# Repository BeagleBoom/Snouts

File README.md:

# 

----
----

**CURRENTLY BROKEN, DO NOT USE OR YOUR BEAGLE BONE COULD BREAK**
>The PCB currently contains a bug with the power-supply which could kill your beagle boom :-/

----
----

This repository contains the BeagleBoom Snouts' PCB layouts.

# About this repository
This repository is part of the [BeagleBoom](https://github.com/beagleboom)-Sampler project developed by the academic working group "[Creative Technologies AG](http://www.creative-technologies.de/)" (ctag) at the [University of Applied Sciences Kiel](https://www.fh-kiel.de/).

The `Sampler` folder holds the PCB which is connected to the BeagleBone. It holds the power source, adc and level shifter.
The `Sampler UI` folder contains the front PCB with all the buttons, jacks, rotaries and lcd port, with all the needed resistors. 

# License
The content and source code of this project itself is licensed under the [Creative Commons Attribution 4.0 International license](https://creativecommons.org/licenses/by/4.0/).

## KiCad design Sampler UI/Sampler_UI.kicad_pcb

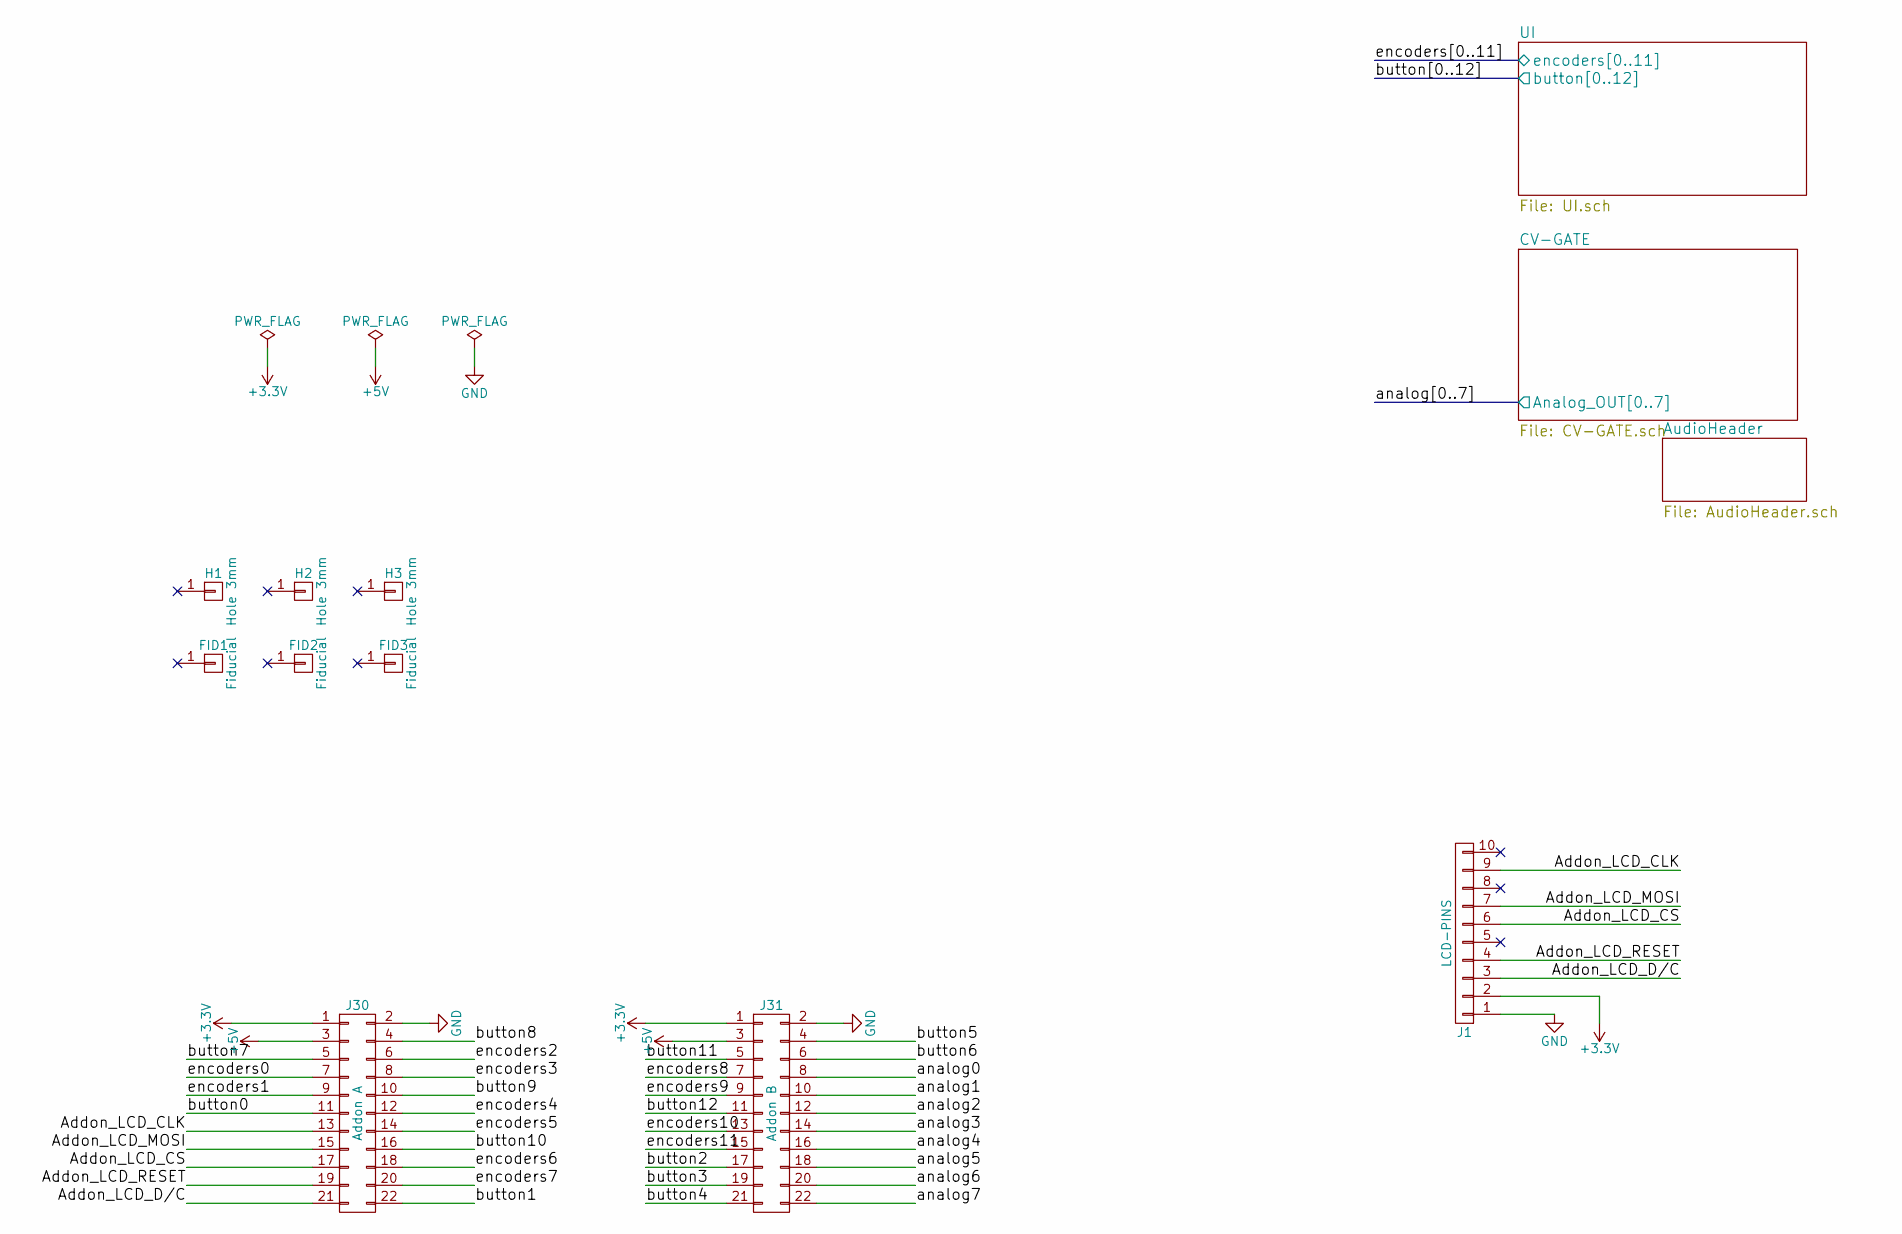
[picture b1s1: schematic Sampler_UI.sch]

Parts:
FID1, FID2, FID3: Fiducial; Fiducial_1mm_Dia_2.54mm_Outer_CopperTop
H1, H2, H3: Hole 3mm; hole_3mm
J1: LCD-PINS; Pin_Header_Straight_1x10_Pitch2.54mm
J30: Addon A; Pin_Header_Straight_2x11_Pitch2.54mm
J31: Addon B; Pin_Header_Straight_2x11_Pitch2.54mm

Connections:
+3V3: J1.2, J30.1, J31.1; also elsewhere on the board
+5V: J30.3, J31.3; also elsewhere on the board
/Addon_LCD_CLK: J1.9, J30.13
/Addon_LCD_CS: J1.6, J30.17
/Addon_LCD_D/C: J1.3, J30.21
/Addon_LCD_MOSI: J1.7, J30.15
/Addon_LCD_RESET: J1.4, J30.19
/analog0: J31.8; also elsewhere on the board
/analog1: J31.10; also elsewhere on the board
/analog2: J31.12; also elsewhere on the board
/analog3: J31.14; also elsewhere on the board
/analog4: J31.16; also elsewhere on the board
/analog5: J31.18; also elsewhere on the board
/analog6: J31.20; also elsewhere on the board
/analog7: J31.22; also elsewhere on the board
/button0: J30.11; also elsewhere on the board
/button1: J30.22; also elsewhere on the board
/button2: J31.17; also elsewhere on the board
/button3: J31.19; also elsewhere on the board
/button4: J31.21; also elsewhere on the board
/button5: J31.4; also elsewhere on the board
/button6: J31.6; also elsewhere on the board
/button7: J30.5; also elsewhere on the board
/button8: J30.4; also elsewhere on the board
/button9: J30.10; also elsewhere on the board
/button10: J30.16; also elsewhere on the board
/button11: J31.5; also elsewhere on the board
/button12: J31.11; also elsewhere on the board
/encoders0: J30.7; also elsewhere on the board
/encoders1: J30.9; also elsewhere on the board
/encoders2: J30.6; also elsewhere on the board
/encoders3: J30.8; also elsewhere on the board
/encoders4: J30.12; also elsewhere on the board
/encoders5: J30.14; also elsewhere on the board
/encoders6: J30.18; also elsewhere on the board
/encoders7: J30.20; also elsewhere on the board
/encoders8: J31.7; also elsewhere on the board
/encoders9: J31.9; also elsewhere on the board
/encoders10: J31.13; also elsewhere on the board
/encoders11: J31.15; also elsewhere on the board
GND: J1.1, J30.2, J31.2; also elsewhere on the board

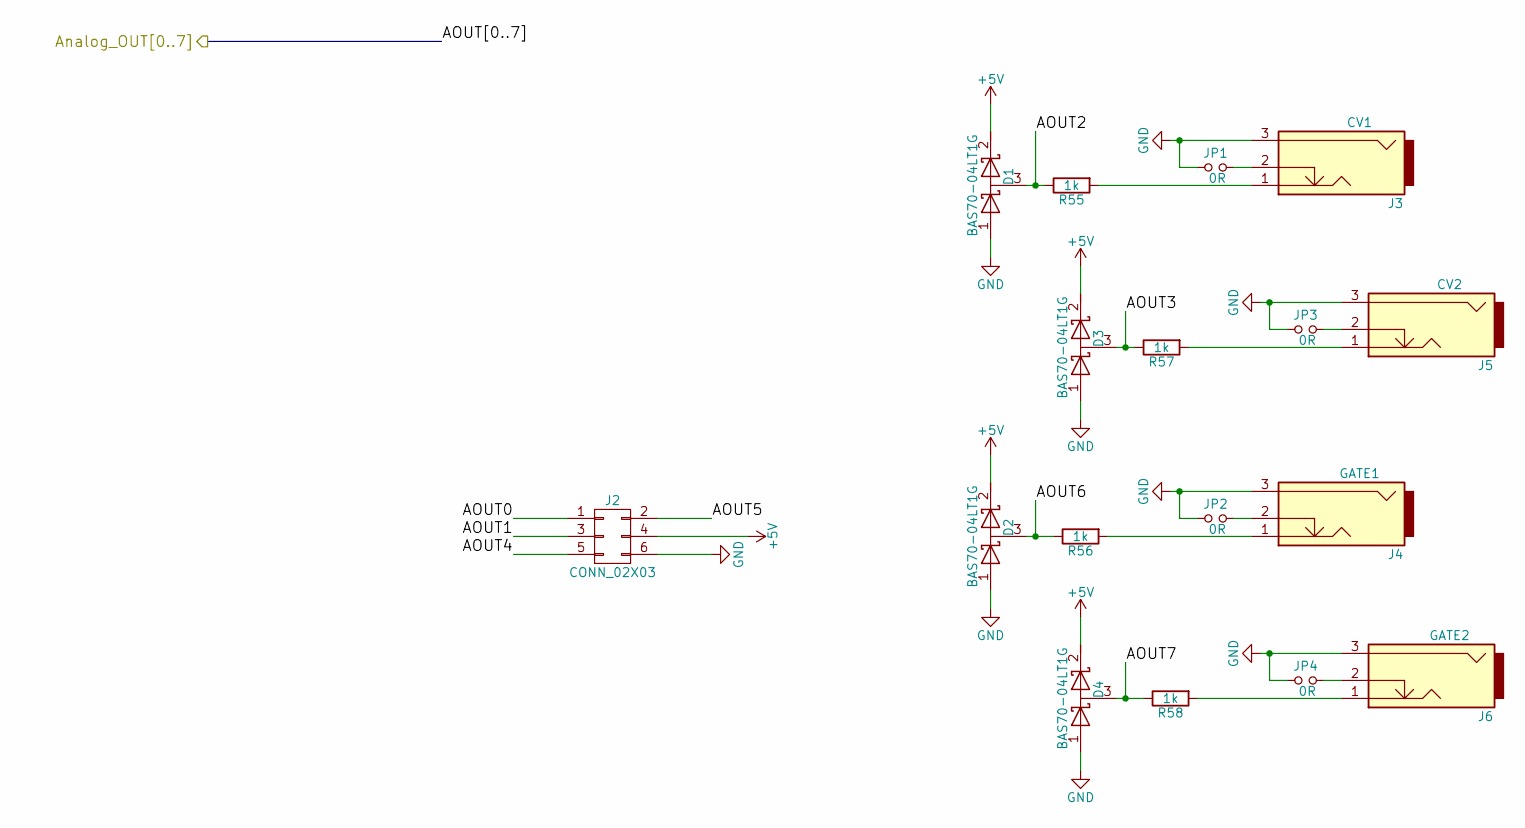
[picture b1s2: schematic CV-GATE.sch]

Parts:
D1, D2, D3, D4: BAS70-04LT1G; SOT-23_Handsoldering
J2: CONN_02X03; Pin_Header_Straight_2x03_Pitch2.54mm
J3: CV1; THONKICONN
J4: GATE1; THONKICONN
J5: CV2; THONKICONN
J6: GATE2; THONKICONN
JP1: 0R; SW_NKK_G1xJP
JP2, JP3, JP4: 0R; C_0603_HandSoldering
R55, R56, R57, R58: 1k; C_0603_HandSoldering

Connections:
+5V: D1.2 (K), D2.2 (K), D3.2 (K), D4.2 (K), J2.4; also elsewhere on the board
/analog0: J2.1; also elsewhere on the board
/analog1: J2.3; also elsewhere on the board
/analog2: D1.3 (common), R55.1; also elsewhere on the board
/analog3: D3.3 (common), R57.1; also elsewhere on the board
/analog4: J2.5; also elsewhere on the board
/analog5: J2.2; also elsewhere on the board
/analog6: D2.3 (common), R56.1; also elsewhere on the board
/analog7: D4.3 (common), R58.1; also elsewhere on the board
GND: D1.1 (A), D2.1 (A), D3.1 (A), D4.1 (A), J2.6, J3.3, J4.3, J5.3, J6.3, JP1.1, JP2.1, JP3.1, JP4.1; also elsewhere on the board
unnamed: J3.1, R55.2
unnamed: J3.2, JP1.2
unnamed: J4.1, R56.2
unnamed: J4.2, JP2.2
unnamed: J5.1, R57.2
unnamed: J5.2, JP3.2
unnamed: J6.1, R58.2
unnamed: J6.2, JP4.2

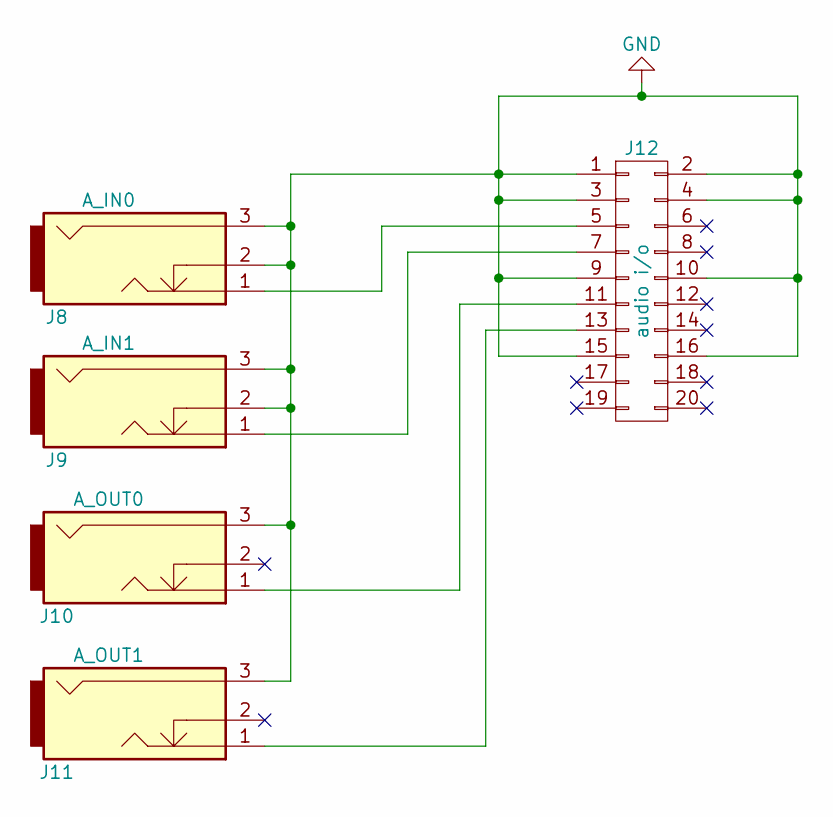
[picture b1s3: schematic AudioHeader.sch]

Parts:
J8: A_IN0; THONKICONN
J9: A_IN1; THONKICONN
J10: A_OUT0; THONKICONN
J11: A_OUT1; THONKICONN
J12: audio i/o; Pin_Header_Straight_2x10_Pitch2.54mm

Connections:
GND: J8.2, J8.3, J9.2, J9.3, J10.3, J11.3, J12.1, J12.2, J12.3, J12.4, J12.9, J12.10, J12.15, J12.16; also elsewhere on the board
unnamed: J10.1, J12.11
unnamed: J11.1, J12.13
unnamed: J8.1, J12.5
unnamed: J9.1, J12.7

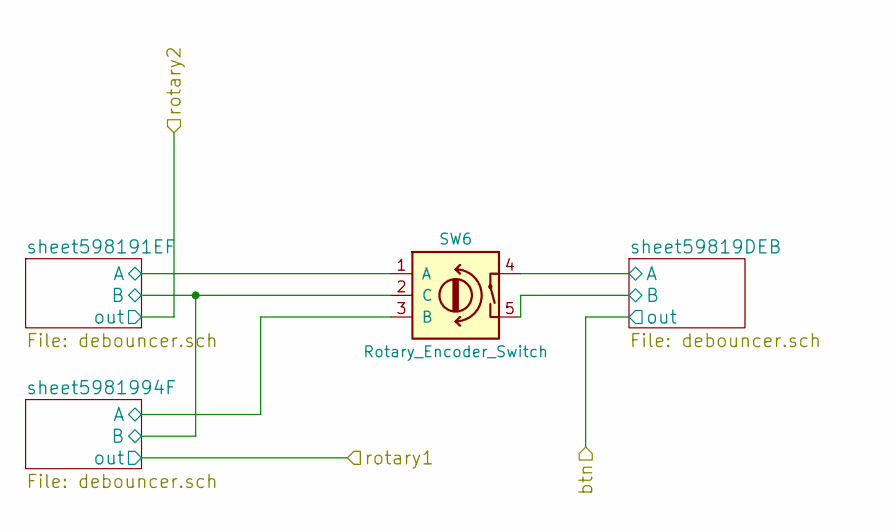
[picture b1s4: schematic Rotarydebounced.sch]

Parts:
SW1: Rotary_Encoder_Switch; ALPS_EC11E

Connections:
/UI/Sheet59818EE0/sheet59819DEB/A: SW1.4; also elsewhere on the board
/UI/Sheet59818EE0/sheet598191EF/A: SW1.1 (A); also elsewhere on the board
/UI/Sheet59818EE0/sheet5981994F/A: SW1.3 (B); also elsewhere on the board
GND: SW1.2 (C), SW1.5; also elsewhere on the board

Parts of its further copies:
SW2, SW3, SW4, SW5, SW6: Rotary_Encoder_Switch; ALPS_EC11E

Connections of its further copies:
/UI/sheet5981BCBF/sheet59819DEB/A: SW2.4; also elsewhere on the board
/UI/sheet5981BCBF/sheet598191EF/A: SW2.1 (A); also elsewhere on the board
/UI/sheet5981BCBF/sheet5981994F/A: SW2.3 (B); also elsewhere on the board
/UI/sheet5981BE21/sheet59819DEB/A: SW3.4; also elsewhere on the board
/UI/sheet5981BE21/sheet598191EF/A: SW3.1 (A); also elsewhere on the board
/UI/sheet5981BE21/sheet5981994F/A: SW3.3 (B); also elsewhere on the board
/UI/sheet5981BFDD/sheet59819DEB/A: SW4.4; also elsewhere on the board
/UI/sheet5981BFDD/sheet598191EF/A: SW4.1 (A); also elsewhere on the board
/UI/sheet5981BFDD/sheet5981994F/A: SW4.3 (B); also elsewhere on the board
/UI/sheet5981C76E/sheet59819DEB/A: SW6.4; also elsewhere on the board
/UI/sheet5981C76E/sheet598191EF/A: SW6.1 (A); also elsewhere on the board
/UI/sheet5981C76E/sheet5981994F/A: SW6.3 (B); also elsewhere on the board
/UI/sheet5981C561/sheet59819DEB/A: SW5.4; also elsewhere on the board
/UI/sheet5981C561/sheet598191EF/A: SW5.1 (A); also elsewhere on the board
/UI/sheet5981C561/sheet5981994F/A: SW5.3 (B); also elsewhere on the board
GND: SW2.2 (C), SW2.5, SW3.2 (C), SW3.5, SW4.2 (C), SW4.5, SW5.2 (C), SW5.5, SW6.2 (C), SW6.5; also elsewhere on the board

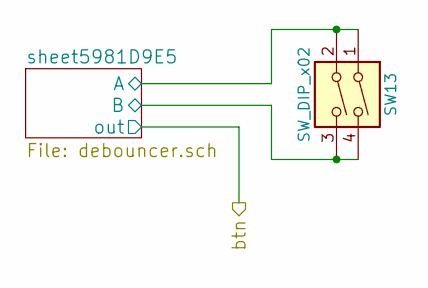
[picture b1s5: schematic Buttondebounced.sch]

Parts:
SW7: SW_DIP_x02; TL1105

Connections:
/UI/Sheet5981D5D9/sheet5981D9E5/A: SW7.1, SW7.2; also elsewhere on the board
GND: SW7.3, SW7.4; also elsewhere on the board

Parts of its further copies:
SW8, SW9, SW10, SW11, SW12, SW13: SW_DIP_x02; TL1105

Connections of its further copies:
/UI/sheet5981FF0E/sheet5981D9E5/A: SW8.1, SW8.2; also elsewhere on the board
/UI/sheet5981FFD8/sheet5981D9E5/A: SW9.1, SW9.2; also elsewhere on the board
/UI/sheet598200A2/sheet5981D9E5/A: SW10.1, SW10.2; also elsewhere on the board
/UI/sheet598202F9/sheet5981D9E5/A: SW11.1, SW11.2; also elsewhere on the board
/UI/sheet598203D2/sheet5981D9E5/A: SW12.1, SW12.2; also elsewhere on the board
/UI/sheet598204B4/sheet5981D9E5/A: SW13.1, SW13.2; also elsewhere on the board
GND: SW8.3, SW8.4, SW9.3, SW9.4, SW10.3, SW10.4, SW11.3, SW11.4, SW12.3, SW12.4, SW13.3, SW13.4; also elsewhere on the board

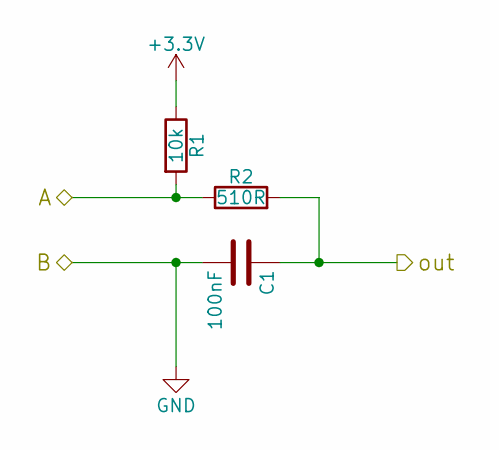
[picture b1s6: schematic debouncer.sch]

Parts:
C1: 100nF; C_0603_HandSoldering
R1: 10k; C_0603_HandSoldering
R2: 510R; C_0603_HandSoldering

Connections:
+3V3: R1.1; also elsewhere on the board
/UI/Sheet59818EE0/sheet598191EF/A: R1.2, R2.1; also elsewhere on the board
/encoders1: C1.1, R2.2; also elsewhere on the board
GND: C1.2; also elsewhere on the board

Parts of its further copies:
C2, C3, C4, C5, C6, C7, C8, C9, C10, C11, C12, C13, C14, C15, C16, C17, C18, C19, C20, C21, C22, C23, C24, C25: 100nF; C_0603_HandSoldering
R3, R5, R7, R9, R11, R13, R15, R17, R19, R21, R23, R25, R27, R29, R31, R33, R35, R37, R39, R41, R43, R45, R47, R49: 10k; C_0603_HandSoldering
R4, R6, R8, R10, R12, R14, R16, R18, R20, R22, R24, R26, R28, R30, R32, R34, R36, R38, R40, R42, R44, R46, R48, R50: 510R; C_0603_HandSoldering

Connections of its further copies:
+3V3: R3.1, R5.1, R7.1, R9.1, R11.1, R13.1, R15.1, R17.1, R19.1, R21.1, R23.1, R25.1, R27.1, R29.1, R31.1, R33.1, R35.1, R37.1, R39.1, R41.1, R43.1, R45.1, R47.1, R49.1; also elsewhere on the board
/UI/Sheet5981D5D9/sheet5981D9E5/A: R37.2, R38.1; also elsewhere on the board
/UI/Sheet59818EE0/sheet59819DEB/A: R5.2, R6.1; also elsewhere on the board
/UI/Sheet59818EE0/sheet5981994F/A: R3.2, R4.1; also elsewhere on the board
/UI/sheet5981BCBF/sheet59819DEB/A: R11.2, R12.1; also elsewhere on the board
/UI/sheet5981BCBF/sheet598191EF/A: R7.2, R8.1; also elsewhere on the board
/UI/sheet5981BCBF/sheet5981994F/A: R9.2, R10.1; also elsewhere on the board
/UI/sheet5981BE21/sheet59819DEB/A: R17.2, R18.1; also elsewhere on the board
/UI/sheet5981BE21/sheet598191EF/A: R13.2, R14.1; also elsewhere on the board
/UI/sheet5981BE21/sheet5981994F/A: R15.2, R16.1; also elsewhere on the board
/UI/sheet5981BFDD/sheet59819DEB/A: R23.2, R24.1; also elsewhere on the board
/UI/sheet5981BFDD/sheet598191EF/A: R19.2, R20.1; also elsewhere on the board
/UI/sheet5981BFDD/sheet5981994F/A: R21.2, R22.1; also elsewhere on the board
/UI/sheet5981C76E/sheet59819DEB/A: R35.2, R36.1; also elsewhere on the board
/UI/sheet5981C76E/sheet598191EF/A: R31.2, R32.1; also elsewhere on the board
/UI/sheet5981C76E/sheet5981994F/A: R33.2, R34.1; also elsewhere on the board
/UI/sheet5981C561/sheet59819DEB/A: R29.2, R30.1; also elsewhere on the board
/UI/sheet5981C561/sheet598191EF/A: R25.2, R26.1; also elsewhere on the board
/UI/sheet5981C561/sheet5981994F/A: R27.2, R28.1; also elsewhere on the board
/UI/sheet5981FF0E/sheet5981D9E5/A: R39.2, R40.1; also elsewhere on the board
/UI/sheet5981FFD8/sheet5981D9E5/A: R41.2, R42.1; also elsewhere on the board
/UI/sheet598200A2/sheet5981D9E5/A: R43.2, R44.1; also elsewhere on the board
/UI/sheet598202F9/sheet5981D9E5/A: R45.2, R46.1; also elsewhere on the board
/UI/sheet598203D2/sheet5981D9E5/A: R47.2, R48.1; also elsewhere on the board
/UI/sheet598204B4/sheet5981D9E5/A: R49.2, R50.1; also elsewhere on the board
/button0: C19.1, R38.2; also elsewhere on the board
/button1: C20.1, R40.2; also elsewhere on the board
/button2: C21.1, R42.2; also elsewhere on the board
/button3: C22.1, R44.2; also elsewhere on the board
/button4: C23.1, R46.2; also elsewhere on the board
/button5: C24.1, R48.2; also elsewhere on the board
/button6: C25.1, R50.2; also elsewhere on the board
/button7: C3.1, R6.2; also elsewhere on the board
/button8: C6.1, R12.2; also elsewhere on the board
/button9: C9.1, R18.2; also elsewhere on the board
/button10: C12.1, R24.2; also elsewhere on the board
/button11: C15.1, R30.2; also elsewhere on the board
/button12: C18.1, R36.2; also elsewhere on the board
/encoders0: C2.1, R4.2; also elsewhere on the board
/encoders2: C5.1, R10.2; also elsewhere on the board
/encoders3: C4.1, R8.2; also elsewhere on the board
/encoders4: C8.1, R16.2; also elsewhere on the board
/encoders5: C7.1, R14.2; also elsewhere on the board
/encoders6: C11.1, R22.2; also elsewhere on the board
/encoders7: C10.1, R20.2; also elsewhere on the board
/encoders8: C14.1, R28.2; also elsewhere on the board
/encoders9: C13.1, R26.2; also elsewhere on the board
/encoders10: C17.1, R34.2; also elsewhere on the board
/encoders11: C16.1, R32.2; also elsewhere on the board
GND: C2.2, C3.2, C4.2, C5.2, C6.2, C7.2, C8.2, C9.2, C10.2, C11.2, C12.2, C13.2, C14.2, C15.2, C16.2, C17.2, C18.2, C19.2, C20.2, C21.2, C22.2, C23.2, C24.2, C25.2; also elsewhere on the board

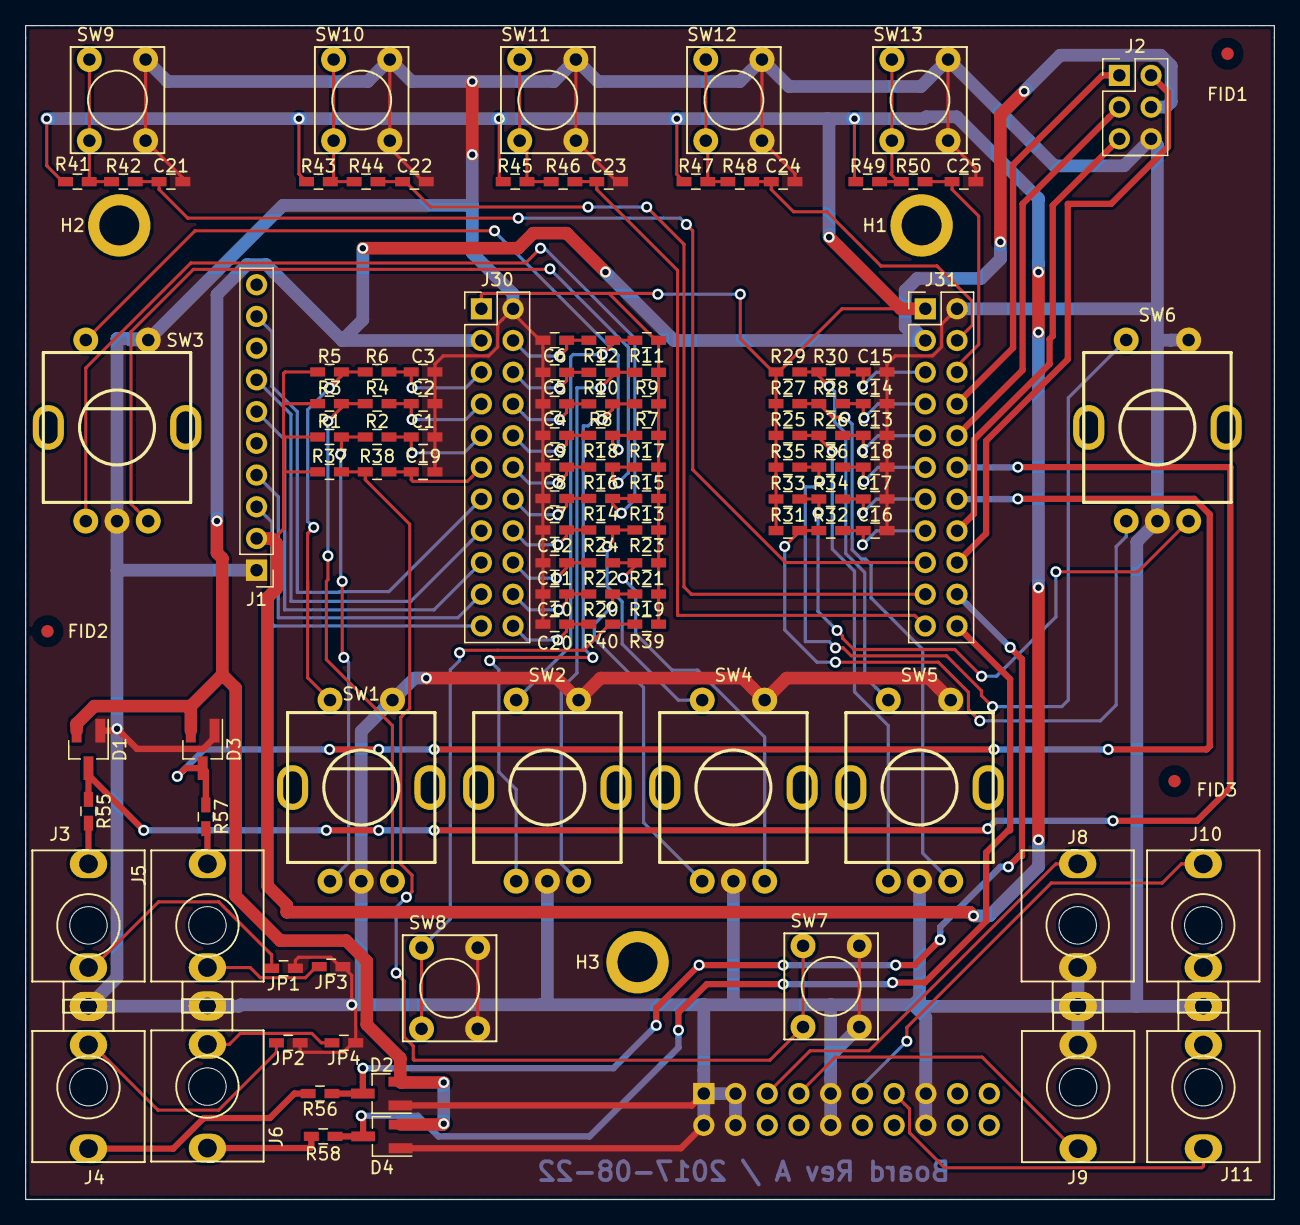
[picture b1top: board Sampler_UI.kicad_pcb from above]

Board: 2 copper layers, 100.0 x 94.0 mm, 119 parts (1 on the bottom side), 78 nets.

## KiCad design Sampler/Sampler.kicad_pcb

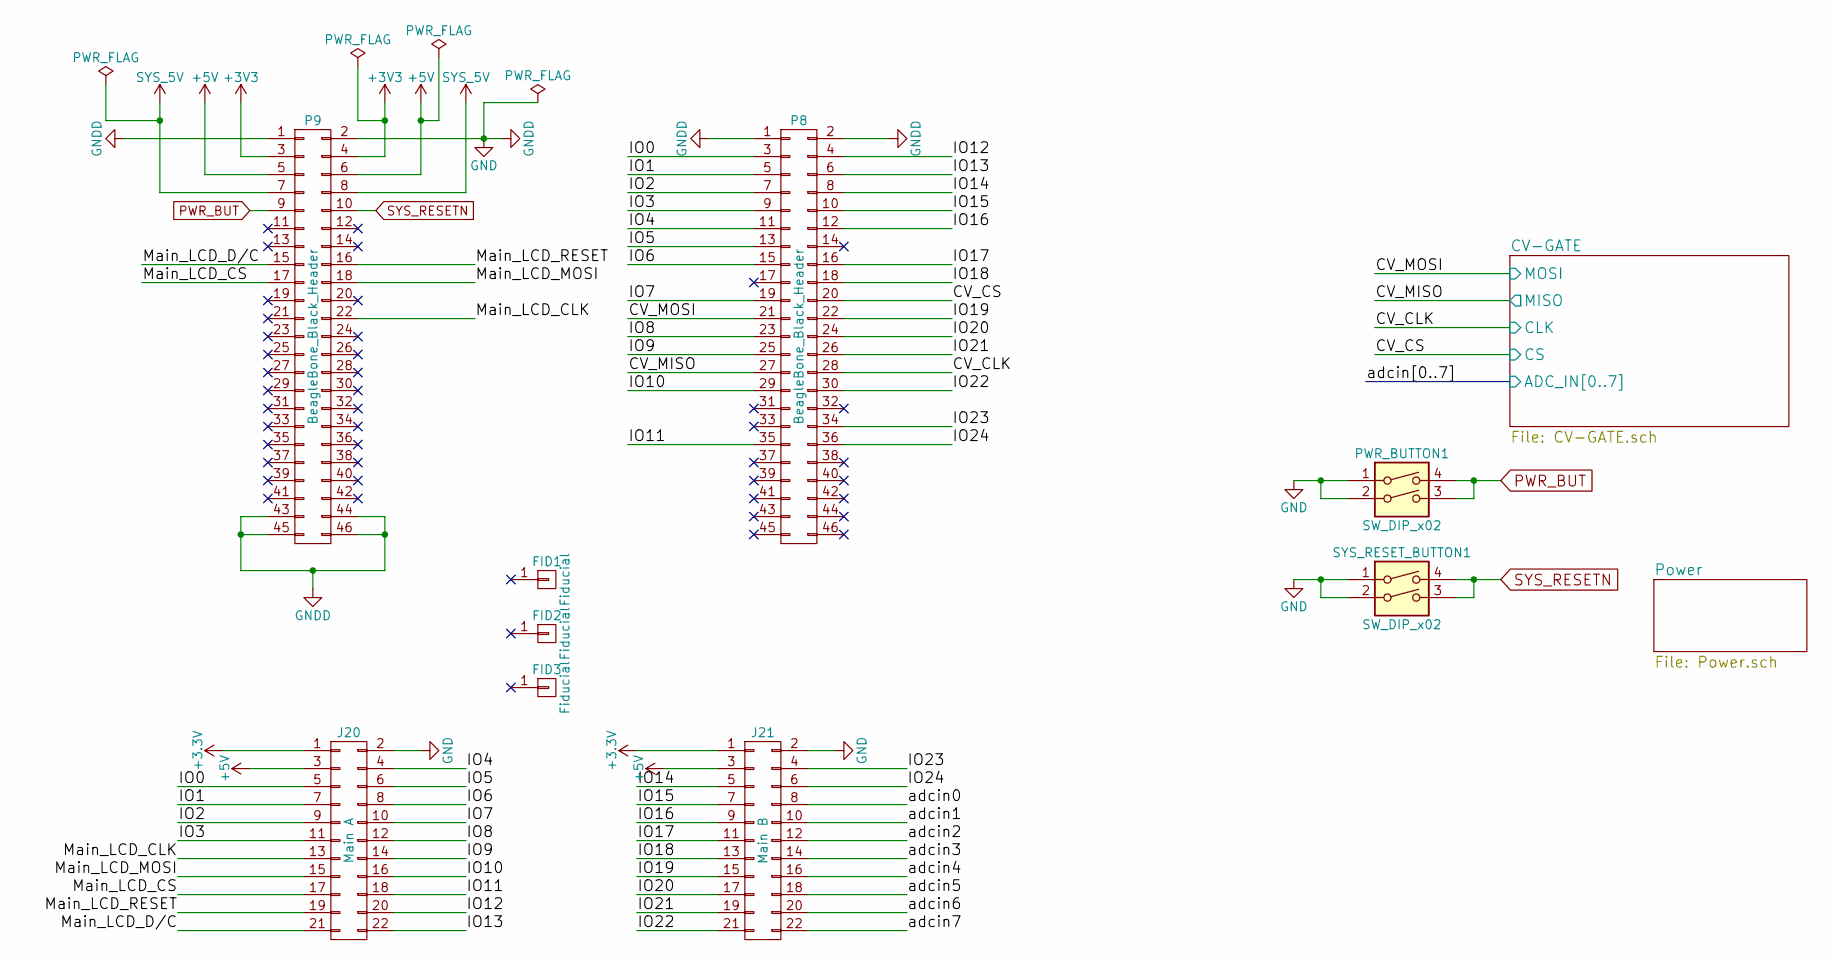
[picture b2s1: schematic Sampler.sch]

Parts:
FID1, FID2, FID3: Fiducial; Fiducial_1mm_Dia_2.54mm_Outer_CopperTop
J20: Main A; Pin_Header_Straight_2x11_Pitch2.54mm
J21: Main B; Pin_Header_Straight_2x11_Pitch2.54mm
P8, P9: BeagleBone_Black_Header; Socket_BeagleBone_Black
PWR_BUTTON1: SW_DIP_x02; TL1105
SYS_RESET_BUTTON1: SW_DIP_x02; TL1105

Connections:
+5V: J20.3, J21.3, P9.5, P9.6; also elsewhere on the board
/CV_CLK: P8.28; also elsewhere on the board
/CV_CS: P8.20; also elsewhere on the board
/CV_MISO: P8.27; also elsewhere on the board
/CV_MOSI: P8.21; also elsewhere on the board
/IO0: J20.5, P8.3
/IO1: J20.7, P8.5
/IO2: J20.9, P8.7
/IO3: J20.11, P8.9
/IO4: J20.4, P8.11
/IO5: J20.6, P8.13
/IO6: J20.8, P8.15
/IO7: J20.10, P8.19
/IO8: J20.12, P8.23
/IO9: J20.14, P8.25
/IO10: J20.16, P8.29
/IO11: J20.18, P8.35
/IO12: J20.20, P8.4
/IO13: J20.22, P8.6
/IO14: J21.5, P8.8
/IO15: J21.7, P8.10
/IO16: J21.9, P8.12
/IO17: J21.11, P8.16
/IO18: J21.13, P8.18
/IO19: J21.15, P8.22
/IO20: J21.17, P8.24
/IO21: J21.19, P8.26
/IO22: J21.21, P8.30
/IO23: J21.4, P8.34
/IO24: J21.6, P8.36
/Main_LCD_CLK: J20.13, P9.22
/Main_LCD_CS: J20.17, P9.17
/Main_LCD_D/C: J20.21, P9.15
/Main_LCD_MOSI: J20.15, P9.18
/Main_LCD_RESET: J20.19, P9.16
/adcin0: J21.8; also elsewhere on the board
/adcin1: J21.10; also elsewhere on the board
/adcin2: J21.12; also elsewhere on the board
/adcin3: J21.14; also elsewhere on the board
/adcin4: J21.16; also elsewhere on the board
/adcin5: J21.18; also elsewhere on the board
/adcin6: J21.20; also elsewhere on the board
/adcin7: J21.22; also elsewhere on the board
GND: J20.2, J21.2, P8.1, P8.2, P9.1, P9.2, P9.43, P9.44, P9.45, P9.46, PWR_BUTTON1.1, PWR_BUTTON1.2, SYS_RESET_BUTTON1.1, SYS_RESET_BUTTON1.2; also elsewhere on the board
PWR_BUT: P9.9, PWR_BUTTON1.3, PWR_BUTTON1.4
SYS_5V: P9.7, P9.8
SYS_RESETN: P9.10, SYS_RESET_BUTTON1.3, SYS_RESET_BUTTON1.4

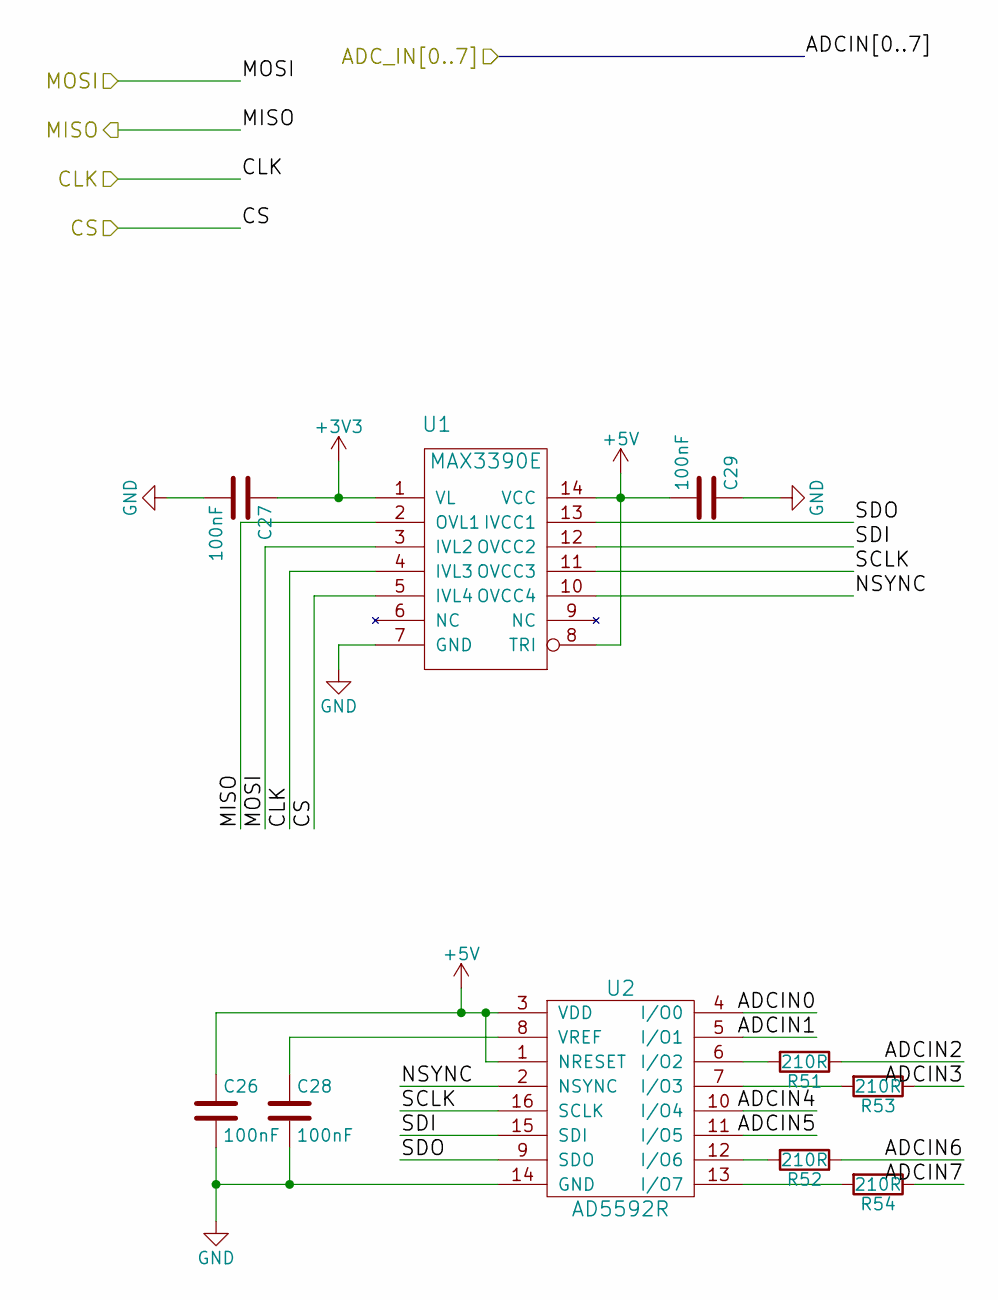
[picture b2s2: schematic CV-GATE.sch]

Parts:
C26, C27, C28, C29: 100nF; C_0603_HandSoldering
R51, R52, R53, R54: 210R; C_0603_HandSoldering
U1: MAX3390E; TSSOP-14_4.4x5mm_Pitch0.65mm
U2: AD5592R; TSSOP-16_4.4x5mm_Pitch0.65mm

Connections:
+5V: C26.1, C29.2, U1.8 (TRI), U1.14 (VCC), U2.1 (NRESET), U2.3 (VDD); also elsewhere on the board
/CV-GATE/NSYNC: U1.10 (OVCC4), U2.2 (NSYNC)
/CV-GATE/SCLK: U1.11 (OVCC3), U2.16 (SCLK)
/CV-GATE/SDI: U1.12 (OVCC2), U2.15 (SDI)
/CV-GATE/SDO: U1.13 (IVCC1), U2.9 (SDO)
/CV_CLK: U1.4 (IVL3); also elsewhere on the board
/CV_CS: U1.5 (IVL4); also elsewhere on the board
/CV_MISO: U1.2 (OVL1); also elsewhere on the board
/CV_MOSI: U1.3 (IVL2); also elsewhere on the board
/adcin0: U2.4 (I/O0); also elsewhere on the board
/adcin1: U2.5 (I/O1); also elsewhere on the board
/adcin2: R51.1; also elsewhere on the board
/adcin3: R53.1; also elsewhere on the board
/adcin4: U2.10 (I/O4); also elsewhere on the board
/adcin5: U2.11 (I/O5); also elsewhere on the board
/adcin6: R52.1; also elsewhere on the board
/adcin7: R54.1; also elsewhere on the board
GND: C26.2, C27.2, C28.2, C29.1, U1.7 (GND), U2.14 (GND); also elsewhere on the board
unnamed: C28.1, U2.8 (VREF)
unnamed: R51.2, U2.6 (I/O2)
unnamed: R52.2, U2.12 (I/O6)
unnamed: R53.2, U2.7 (I/O3)
unnamed: R54.2, U2.13 (I/O7)

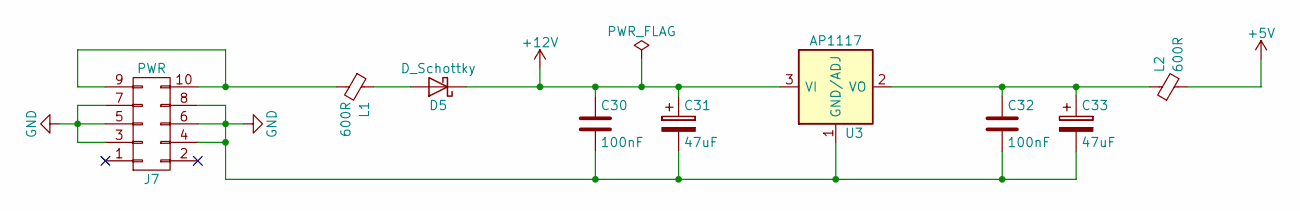
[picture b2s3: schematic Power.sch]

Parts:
C30, C32: 100nF; C_0603_HandSoldering
C31, C33: 47uF; CP_Elec_8x5.4
D5: D_Schottky; D_SOD-323_HandSoldering
J7: PWR; Pin_Header_Straight_2x05_Pitch2.54mm
L1, L2: 600R; C_0805_HandSoldering
U3: AP1117; SOT-223

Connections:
+5V: L2.2; also elsewhere on the board
+12V: C30.1, C31.1, D5.1 (K), U3.3 (VI)
GND: C30.2, C31.2, C32.2, C33.2, J7.3, J7.4, J7.5, J7.6, J7.7, J7.8, U3.1 (GND/ADJ); also elsewhere on the board
unnamed: C32.1, C33.1, L2.1, U3.2 (VO), U3.4 (VO)
unnamed: D5.2 (A), L1.1
unnamed: J7.9, J7.10, L1.2

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
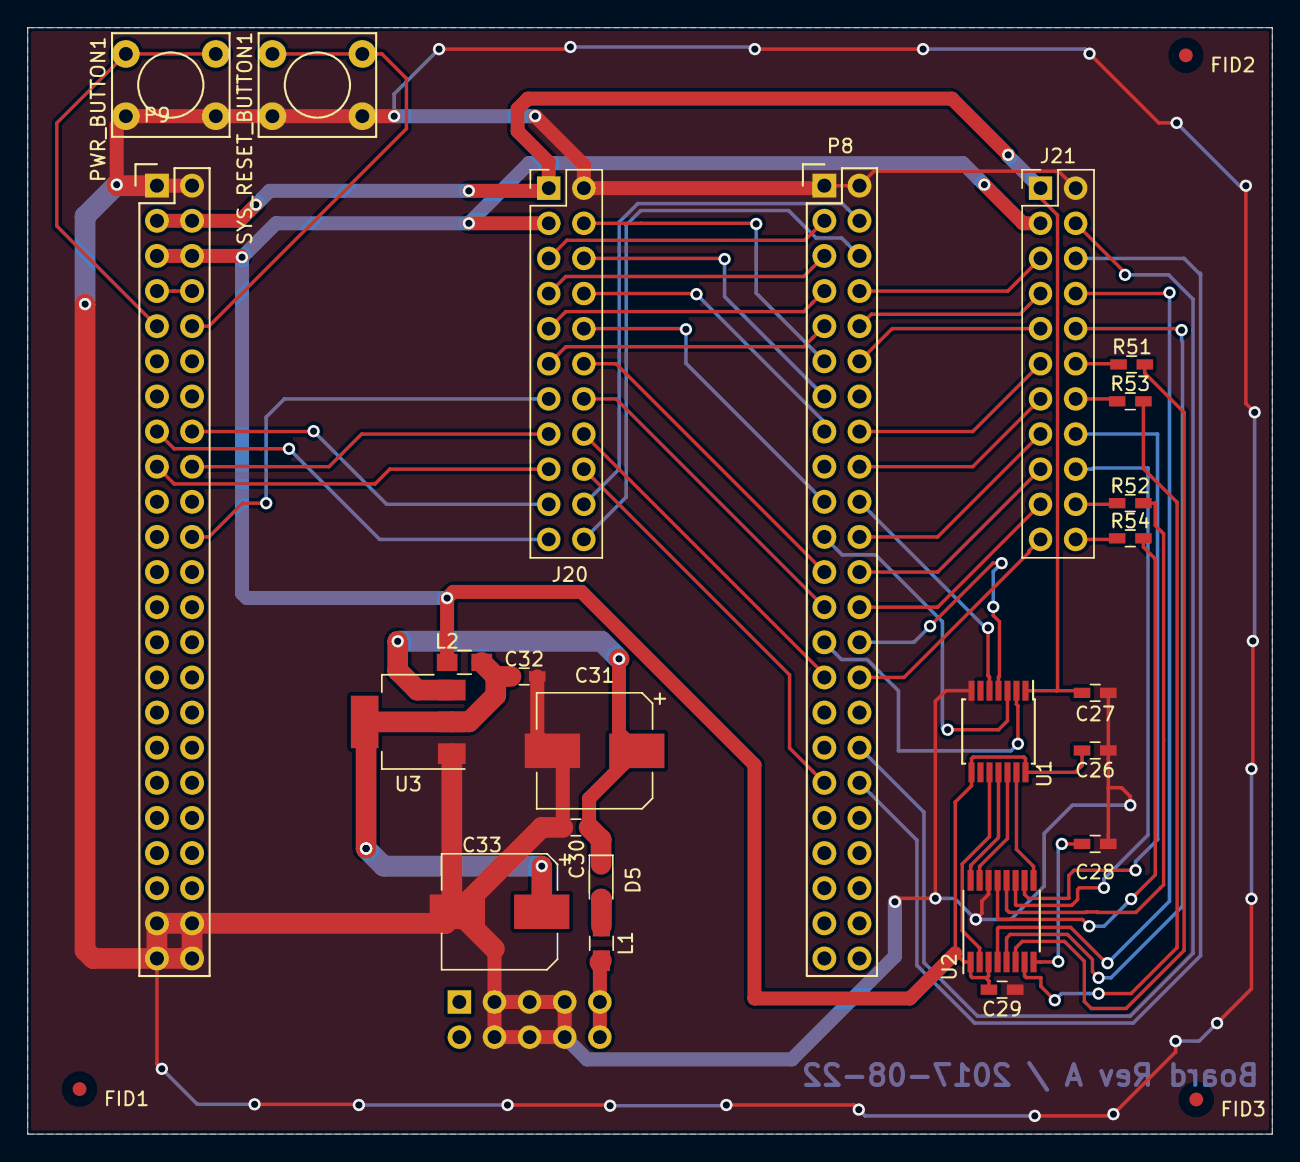
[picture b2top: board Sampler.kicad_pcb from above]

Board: 2 copper layers, 90.0 x 80.0 mm, 28 parts (1 on the bottom side), 61 nets.

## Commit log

2018-08-26 Added Readme, logo and license
2018-08-26 Fixed Readme
2018-08-28 added KiCad files
2018-08-30 closes #1, Added Schematics as PDF
